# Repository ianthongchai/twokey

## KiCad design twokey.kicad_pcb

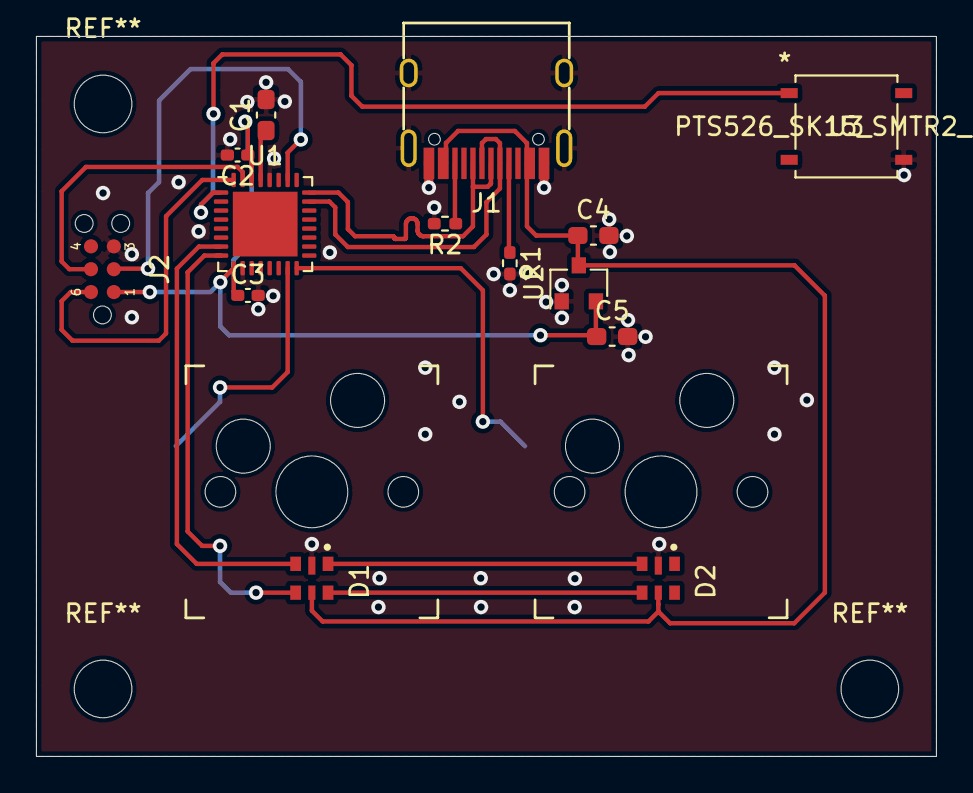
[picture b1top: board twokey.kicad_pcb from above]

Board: 2 copper layers, 50.0 x 40.0 mm, 16 parts (0 on the bottom side), 18 nets.

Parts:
C1, C4, C5: 1uF; C_0603_1608Metric_Pad1.08x0.95mm_HandSolder
C2, C3: 0.1uF; C_0402_1005Metric_Pad0.74x0.62mm_HandSolder
D1, D2: BB-2020BGR-TRB; LED_BB-2020BGR-TRB
J1: 12401610E4#2A; USB_C_Receptacle_GT-USB-7010
J2: Conn_02x03_Odd_Even; TC2030-IDC-NL
R1, R2: 5.1k; R_0402_1005Metric_Pad0.72x0.64mm_HandSolder
SW1, SW2: SW_SPST; Kailh_socket_MX
U1: ATSAMD21E18A-A; QFN-32-1EP_5x5mm_P0.5mm_EP3.6x3.6mm
U2: MCP1700-3302E_SOT23; SOT-23
U3: PTS526_SK15_SMTR2_LFS; PTS526 SK15 SMTR2 LFS

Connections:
+3V3: C2.1, C3.1, C5.1, J2.1, U1.9, U1.30, U2.2
BUTTON: U1.1, U3.1
D+: J1.A6, J1.B6, U1.24
D-: J1.A7, J1.B7, U1.23
GND: C1.2, C2.2, C3.2, C4.2, C5.2, D1.2, D2.2, J1.A1, J1.A12, J1.B1, J1.B12, J1.S1, J2.3, R1.2, R2.2, SW1.1, SW2.1, U1.10, U1.28, U2.1, U3.4
KEY1: SW1.2, U1.16
KEY2: SW2.2, U1.15
LED_CI: D1.4, U1.8
LED_DI: D1.3, U1.7
unnamed: C1.1, U1.29
unnamed: D1.1, D2.3
unnamed: D1.6, D2.4
unnamed: J1.A5, R1.1
unnamed: J1.B5, R2.1
SWCLK: J2.5, U1.31
SWDIO: J2.6, U1.32
VBUS: C4.1, D1.5, D2.5, J1.A4, J1.A9, J1.B4, J1.B9, U2.3
~RESET: J2.2, U1.26

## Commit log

2021-07-18 initial version
2021-07-18 added key switches
2021-07-29 ordered pcb
2021-08-04 First working firmware (disable VBUS detect)
2021-08-04 LEDs first working version
2021-08-09 Bootloader compatibility and polling spi completion.
2021-08-09 Adding bin2uf2.js script to generate uf2 compatible firmware updates.
2021-08-09 switched components to top. ordered new board
2021-08-09 Generating u2f as a post build event.
2021-08-09 Updating .gitignore
2021-08-09 Removing output files from repository
2021-08-09 Ignore local visual studio prefs.
2021-08-10 static, breathing, reactive, static off animations

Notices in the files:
parts and their libraries:
Copyright 2021 Accelerated Designs. All rights reserved.
